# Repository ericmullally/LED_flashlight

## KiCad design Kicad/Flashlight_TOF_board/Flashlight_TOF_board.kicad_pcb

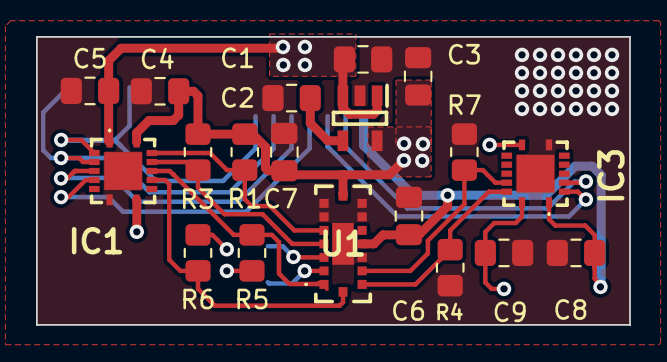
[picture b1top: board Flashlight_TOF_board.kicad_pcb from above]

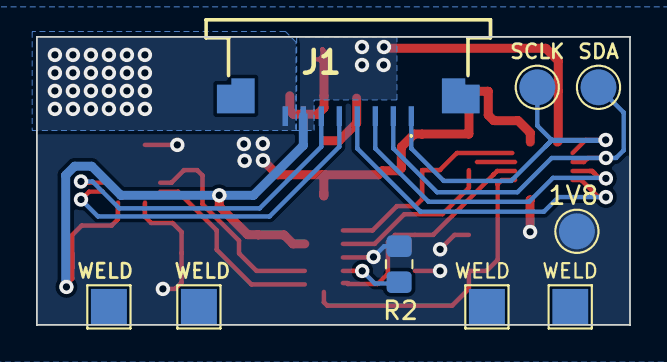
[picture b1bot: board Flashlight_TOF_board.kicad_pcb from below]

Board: 2 copper layers, 33.0 x 16.0 mm, 28 parts (9 on the bottom side), 17 nets.

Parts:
1V8: 1V8_test; TestPoint_Pad_D2.0mm
C1, C2, C3, C4, C5, C6, C7, C9: 100nF; C_0805_2012Metric_Pad1.18x1.45mm_HandSolder
C8: 4uF7; C_0805_2012Metric_Pad1.18x1.45mm_HandSolder
IC1, IC3: PI4ULS3V204ZBEX
IC2: LDK130M18RY; SOT95P280X145-5N
J1: F52R-1A7H1-11008; F52R1A7H111008
R1, R2, R3, R4, R7: 47K; R_0805_2012Metric_Pad1.20x1.40mm_HandSolder
R5, R6: 2K2; R_0805_2012Metric_Pad1.20x1.40mm_HandSolder
SCLK: SCL_test; TestPoint_Pad_D2.0mm
SDA: SDA_test; TestPoint_Pad_D2.0mm
U1: VL53L8CXV0GC_1; VL53L8CXV0GC1
WELD: WELD; TestPoint_Pad_2.0x2.0mm
WELD#2, WELD#3, WELD#4: WELD; TestPoint_Pad_2.0x2.0mm

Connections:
+1V8: 1V8.1, C3.1, C4.1, C7.1, C9.2, IC1.8 (EN), IC1.14 (VCCB), IC2.5 (OUT), IC3.8 (EN), IC3.14 (VCCB), R1.2, R2.2, R3.2, R5.2, R6.2, U1.A3 (IOVDD), U1.B7 (CORE_1V8)
+3V3: C1.1, C5.1, C6.1, C8.1, IC1.1 (VCCA), IC2.1 (IN), IC2.3 (EN), IC3.1 (VCCA), J1.7, U1.C4 (VDD)
DUT_I2C_RESET: IC3.13 (B1), R4.1, U1.C1 (SPI_I2C_N)
DUT_INT: IC1.11 (B3), R5.1, U1.A1 (INT_2)
DUT_NCS: IC3.12 (B2), R7.1, U1.C2 (NCS)
DUT_SCLCK: IC1.13 (B1), R1.1, U1.A5 (MCLK)
DUT_SDA: IC1.12 (B2), R3.1, U1.A4 (MOSI)
DUT_SYNC: IC1.10 (B4), R6.1, U1.B1 (SYNC)
GND: C1.2, C2.2, C3.2, C4.2, C5.2, C6.2, C7.2, C8.2, C9.1, IC1.7 (GND), IC1.15 (EP), IC2.2 (GND), IC3.7 (GND), IC3.15 (EP), J1.8, R4.2, R7.2, U1.A6 (SWD_IO), U1.A7 (SWD_CLK), U1.B4 (GND_1), U1.C3 (GND_2), U1.C6 (ATEST1), U1.C7 (GND_3)
I2C_RESET: IC3.2 (A1), J1.5
INT: IC1.4 (A3), J1.3
NCS: IC3.3 (A2), J1.6
unnamed: C2.1, IC2.4 (BYP/ADJ)
unnamed: R2.1, U1.A2 (XSHUT)
SCLCK: IC1.2 (A1), J1.1, SCLK.1
SDA: IC1.3 (A2), J1.2, SDA.1
SYNC: IC1.5 (A4), J1.4

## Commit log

2024-02-13 reset due to git
2024-02-13 TOF finished
2024-02-21 cosmetic work on tof
